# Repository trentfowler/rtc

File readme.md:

# Real time clock drop-in circuit block/pcb reference

**Description:** KiCad schematic and reference pcb layout for a real time clock that uses the DS1302 rtc chip.

DS1302 - https://datasheets.maximintegrated.com/en/ds/DS1302.pdf

BOM - https://www.digikey.com/short/p2twq1

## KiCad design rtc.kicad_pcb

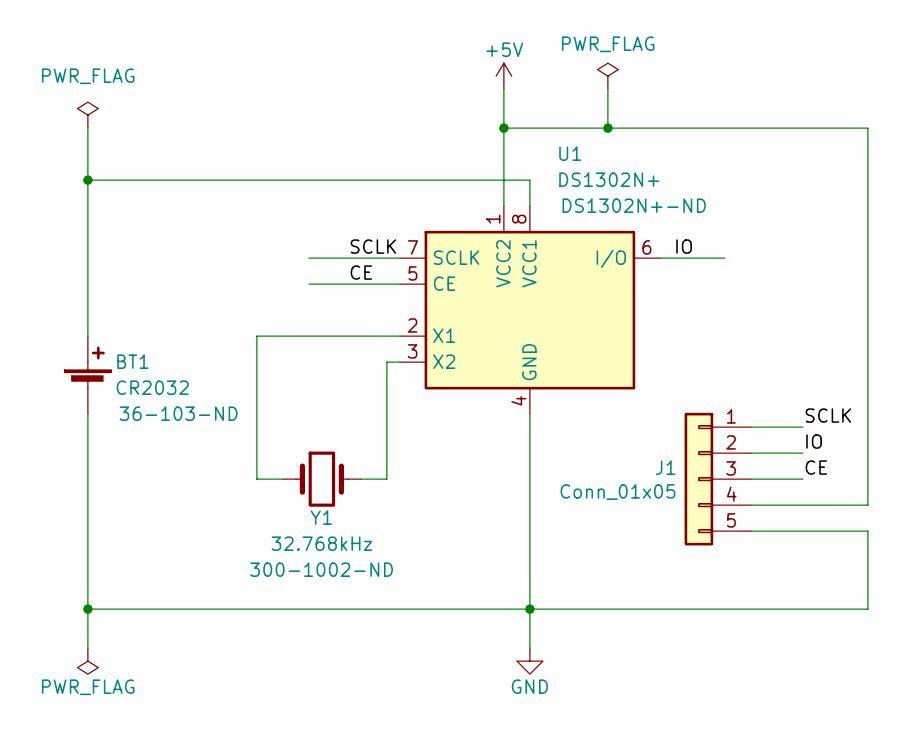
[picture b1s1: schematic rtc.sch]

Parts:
BT1: CR2032; BatteryHolder_Keystone_103_1x20mm; digikey 36-103-ND
J1: Conn_01x05; PinHeader_1x05_P2.54mm_Horizontal
U1: DS1302N+; DIP-8_W7.62mm; digikey DS1302N+-ND
Y1: 32.768kHz; Crystal_Round_D2.0mm_Vertical; digikey 300-1002-ND

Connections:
+5V: J1.4, U1.1 (VCC2)
/CE: J1.3, U1.5 (CE)
/IO: J1.2, U1.6 (I/O)
/SCLK: J1.1, U1.7 (SCLK)
GND: BT1.2 (-), J1.5, U1.4 (GND)
unnamed: BT1.1 (+), U1.8 (VCC1)
unnamed: U1.2 (X1), Y1.1
unnamed: U1.3 (X2), Y1.2

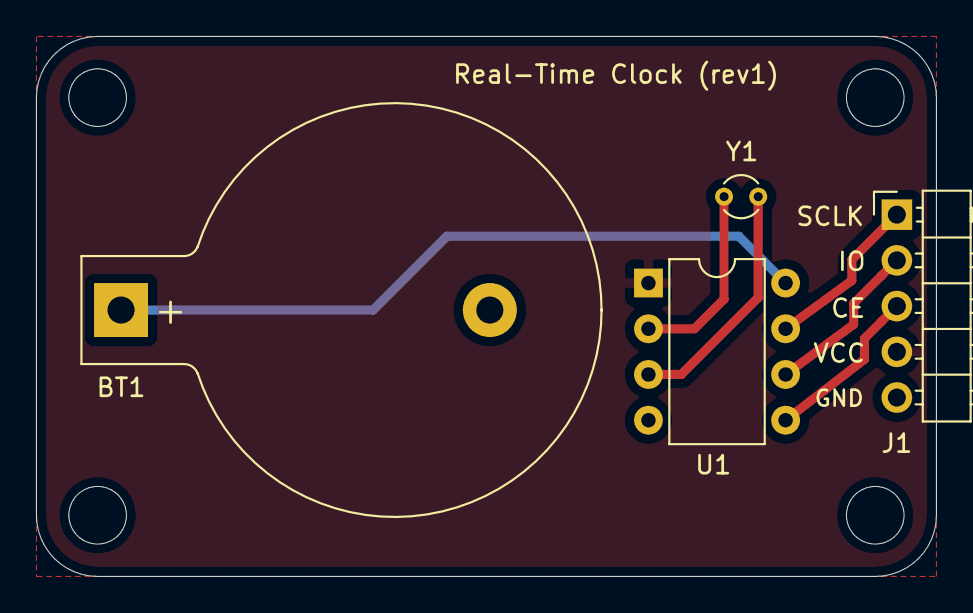
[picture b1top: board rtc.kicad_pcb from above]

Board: 2 copper layers, 50.0 x 30.0 mm, 4 parts (0 on the bottom side), 8 nets.

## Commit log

2019-09-21 Initial commit (schematic only)
2019-09-21 Tweak schematic and add pwr markers. Assign footprints.
    - Generate net list
2019-09-21 Initial pcb layout and routing. Add readme/imgs.
    - Added design rules for oshpark
    - Added mounting holes and 30x50mm board outline
2019-09-22 Remove redundant pull-ups per datasheet
    - Capacitors accross crystal removed per datasheet info on oscillator circuit
2019-09-22 Simplify schematic and update readme
2019-09-22 Simplify by removing pull-ups and bypass cap per datasheet
    - Re-run traces
    - Update img/readme
2019-09-22 Remove front copper polygon fill
    - Clean up labels
2019-09-22 Update images
2019-09-23 Update schematic labels and associate footprints with new digikey component selections
2019-09-23 Redo pcb layout and traces
    - Restored front copper polygon fill
2019-09-23 Clean up silk screen labels
2019-09-23 Round edgecuts
    - New project footprint library rtc.pretty
    - Added logo to silkscreen
    - Added title/rev to silkscreen
2019-09-23 Fix courtyard drc error on keystone 103 holder
    - fix outline on keystone 103 battery holder and move fixed part into
    rtc.pretty
2019-09-23 Add digikey bom or cart share to readme
2019-09-23 final rev1 commit with gerbers folder and gerbers.zip
